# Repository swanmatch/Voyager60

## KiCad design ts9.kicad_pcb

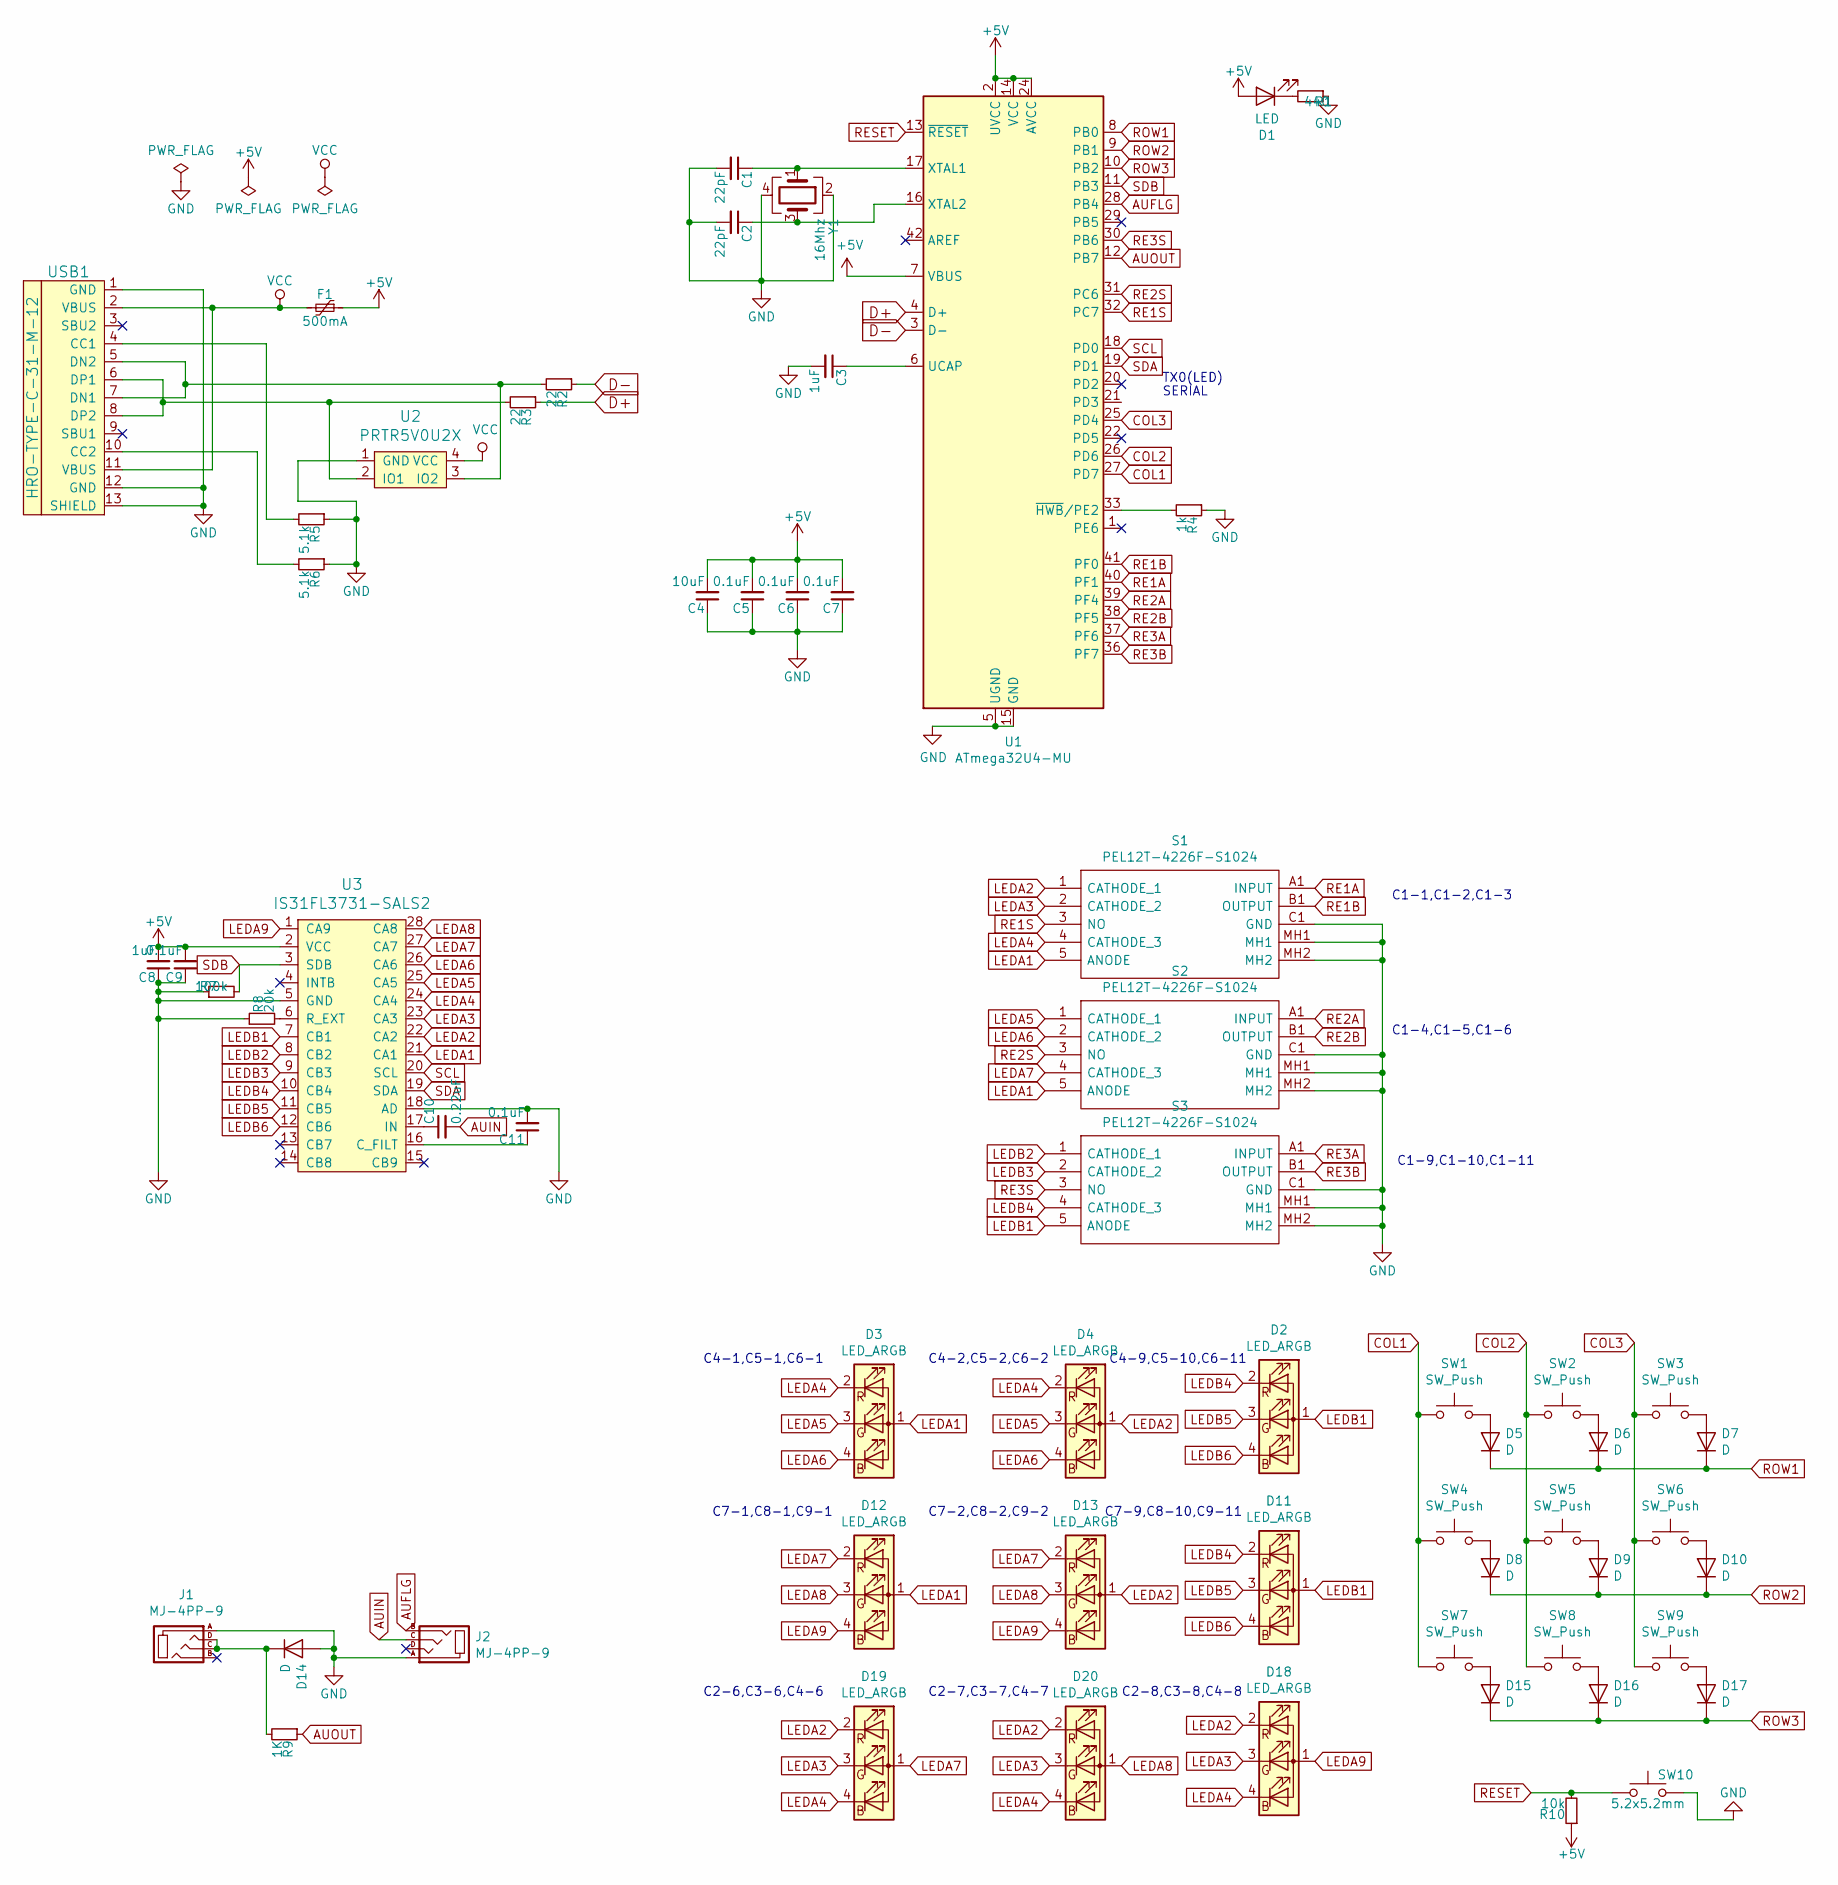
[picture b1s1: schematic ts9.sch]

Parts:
C1, C2: 22pF; C_0603
C3, C8: 1uF; C_0603
C4: 10uF; C_0603
C5, C6, C7, C9, C11: 0.1uF; C_0603
C10: 0.22uF; C_0603
D1: LED; LED_D3.0mm
D2, D3, D4, D11, D12, D13, D18, D19, D20: LED_ARGB; LED_Kingbright_AAA3528ESGCT
D5, D6, D7, D8, D9, D10, D14, D15, D16, D17: D; D_SOD-123
F1: 500mA; Fuse_SMD1206_Reflow
J1, J2: MJ-4PP-9; MJ-4PP-9_1side
R1: 440; R_0805
R2, R3: 22; R_0805
R4: 1k; R_0805
R5, R6: 5.1k; R_0805
R7: 100k; R_0805
R8: 20k; R_0805
R9: 1K; R_0805
R10: 10k; R_0805
S1, S2, S3: PEL12T-4226F-S1024; PEL12T4226FS1024; Manufacturer_Part_Number PEL12T-4226F-S1024; Mouser Part Number 652-PEL12T4226FS1024
SW1, SW2, SW3, SW4, SW5, SW6, SW7, SW8, SW9: SW_Push; PG1350
SW10: 5.2x5.2mm; ResetSW_1side
U1: ATmega32U4-MU; TQFP-44-1EP_10x10mm_Pitch0.8mm
U2: PRTR5V0U2X; SOT143B
U3: IS31FL3731-SALS2; SOP65P780X200-28N
USB1: HRO-TYPE-C-31-M-12; HRO-TYPE-C-31-M-12-Assembly
Y1: 16Mhz; Crystal_SMD_3225-4pin_3.2x2.5mm

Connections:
+5V: C4.2, C5.2, C6.2, C7.2, C8.2, C9.2, D1.2 (A), F1.1, R10.1, U1.2 (UVCC), U1.7 (VBUS), U1.14 (VCC), U1.24 (AVCC), U1.34 (VCC), U1.44 (AVCC), U3.2 (VCC)
AUFLG: J2.B, U1.28 (PB4)
AUIN: C10.2, J2.C
AUOUT: R9.1, U1.12 (PB7)
COL1: SW1.1, SW4.1, SW7.1, U1.27 (PD7)
COL2: SW2.1, SW5.1, SW8.1, U1.26 (PD6)
COL3: SW3.1, SW6.1, SW9.1, U1.25 (PD4)
D+: R3.1, U1.4 (D+)
D-: R2.1, U1.3 (D-)
GND: C1.2, C2.2, C3.2, C4.1, C5.1, C6.1, C7.1, C8.1, C9.1, C11.2, D14.2 (A), J1.A, J2.A, R1.1, R4.1, R5.1, R6.1, R7.1, R8.1, S1.C1 (GND), S1.MH1, S1.MH2, S2.C1 (GND), S2.MH1, S2.MH2, S3.C1 (GND), S3.MH1, S3.MH2, SW10.2, U1.5 (UGND), U1.15 (GND), U1.23 (GND), U1.35 (GND), U1.43 (GND), U1.45 (GND), U2.1 (GND), U3.5 (GND), U3.18 (AD), USB1.1 (GND), USB1.12 (GND), USB1.13 (SHIELD), Y1.2, Y1.4
LEDA1: D3.1 (A), D12.1 (A), S1.5 (ANODE), S2.5 (ANODE), U3.21 (CA1)
LEDA2: D4.1 (A), D13.1 (A), D18.2 (RK), D19.2 (RK), D20.2 (RK), S1.1 (CATHODE_1), U3.22 (CA2)
LEDA3: D18.3 (GK), D19.3 (GK), D20.3 (GK), S1.2 (CATHODE_2), U3.23 (CA3)
LEDA4: D3.2 (RK), D4.2 (RK), D18.4 (BK), D19.4 (BK), D20.4 (BK), S1.4 (CATHODE_3), U3.24 (CA4)
LEDA5: D3.3 (GK), D4.3 (GK), S2.1 (CATHODE_1), U3.25 (CA5)
LEDA6: D3.4 (BK), D4.4 (BK), S2.2 (CATHODE_2), U3.26 (CA6)
LEDA7: D12.2 (RK), D13.2 (RK), D19.1 (A), S2.4 (CATHODE_3), U3.27 (CA7)
LEDA8: D12.3 (GK), D13.3 (GK), D20.1 (A), U3.28 (CA8)
LEDA9: D12.4 (BK), D13.4 (BK), D18.1 (A), U3.1 (CA9)
LEDB1: D2.1 (A), D11.1 (A), S3.5 (ANODE), U3.7 (CB1)
LEDB2: S3.1 (CATHODE_1), U3.8 (CB2)
LEDB3: S3.2 (CATHODE_2), U3.9 (CB3)
LEDB4: D2.2 (RK), D11.2 (RK), S3.4 (CATHODE_3), U3.10 (CB4)
LEDB5: D2.3 (GK), D11.3 (GK), U3.11 (CB5)
LEDB6: D2.4 (BK), D11.4 (BK), U3.12 (CB6)
unnamed: C1.1, U1.17 (XTAL1), Y1.1
unnamed: C2.1, U1.16 (XTAL2), Y1.3
unnamed: C3.1, U1.6 (UCAP)
unnamed: C10.1, U3.17 (IN)
unnamed: C11.1, U3.16 (C_FILT)
unnamed: D1.1 (K), R1.2
unnamed: D5.2 (A), SW1.2
unnamed: D6.2 (A), SW2.2
unnamed: D7.2 (A), SW3.2
unnamed: D8.2 (A), SW4.2
unnamed: D9.2 (A), SW5.2
unnamed: D10.2 (A), SW6.2
unnamed: D14.1 (K), J1.C, J1.D, R9.2
unnamed: D15.2 (A), SW7.2
unnamed: D16.2 (A), SW8.2
unnamed: D17.2 (A), SW9.2
unnamed: R2.2, U2.3 (IO2), USB1.5 (DN2), USB1.7 (DN1)
unnamed: R3.2, U2.2 (IO1), USB1.6 (DP1), USB1.8 (DP2)
unnamed: R4.2, U1.33 (~HWB~/PE2)
unnamed: R5.2, USB1.4 (CC1)
unnamed: R6.2, USB1.10 (CC2)
unnamed: R8.2, U3.6 (R_EXT)
RE1A: S1.A1 (INPUT), U1.40 (PF1)
RE1B: S1.B1 (OUTPUT), U1.41 (PF0)
RE1S: S1.3 (NO), U1.32 (PC7)
RE2A: S2.A1 (INPUT), U1.39 (PF4)
RE2B: S2.B1 (OUTPUT), U1.38 (PF5)
RE2S: S2.3 (NO), U1.31 (PC6)
RE3A: S3.A1 (INPUT), U1.37 (PF6)
RE3B: S3.B1 (OUTPUT), U1.36 (PF7)
RE3S: S3.3 (NO), U1.30 (PB6)
RESET: R10.2, SW10.1, U1.13 (~RESET)
ROW1: D5.1 (K), D6.1 (K), D7.1 (K), U1.8 (PB0)
ROW2: D8.1 (K), D9.1 (K), D10.1 (K), U1.9 (PB1)
ROW3: D15.1 (K), D16.1 (K), D17.1 (K), U1.10 (PB2)
SCL: U1.18 (PD0), U3.20 (SCL)
SDA: U1.19 (PD1), U3.19 (SDA)
SDB: R7.2, U1.11 (PB3), U3.3 (SDB)
VCC: F1.2, U2.4 (VCC), USB1.2 (VBUS), USB1.11 (VBUS)

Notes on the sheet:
TX0(LED)
C1-1,C1-2,C1-3
C1-4,C1-5,C1-6
C1-9,C1-10,C1-11
C4-1,C5-1,C6-1
C7-1,C8-1,C9-1
C4-2,C5-2,C6-2
C7-2,C8-2,C9-2
C4-9,C5-10,C6-11
C7-9,C8-10,C9-11
C2-6,C3-6,C4-6
C2-7,C3-7,C4-7
C2-8,C3-8,C4-8
SERIAL

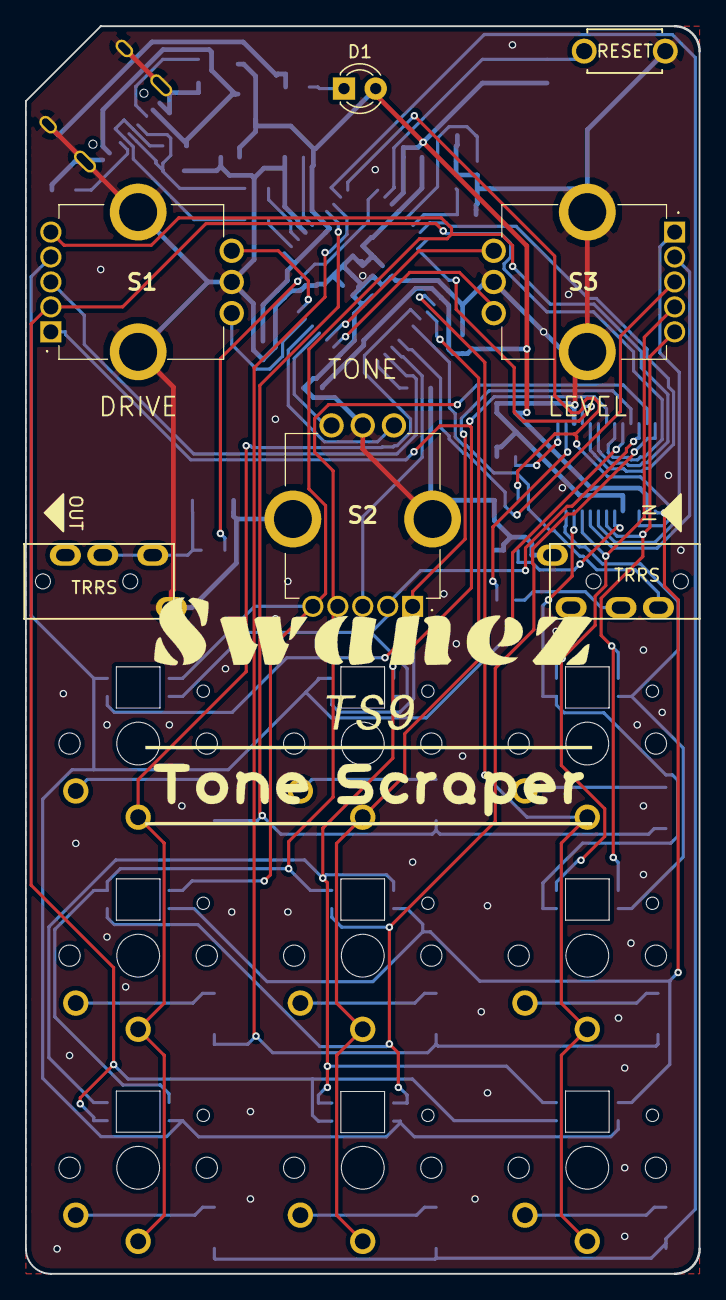
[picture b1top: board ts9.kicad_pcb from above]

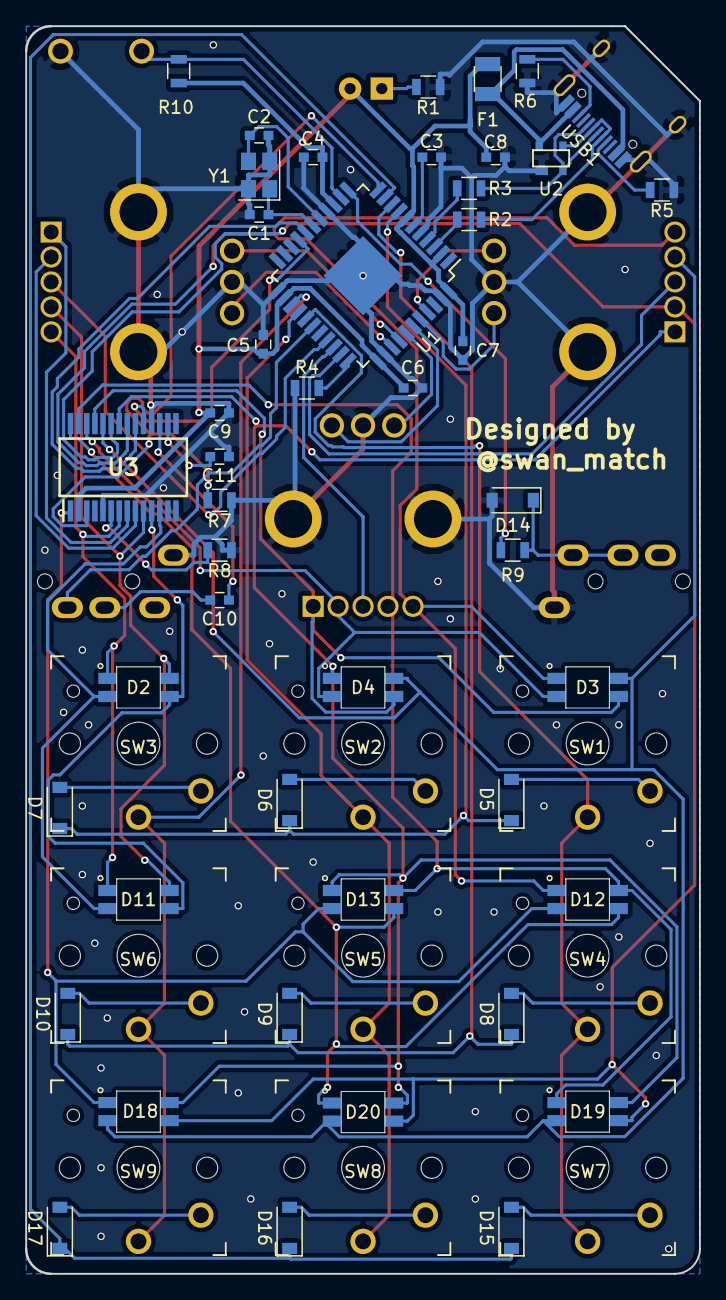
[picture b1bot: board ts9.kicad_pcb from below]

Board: 2 copper layers, 54.0 x 100.0 mm, 62 parts (46 on the bottom side), 64 nets.

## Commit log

2019-11-16 bete
2019-11-16 beta
2019-12-19 first order
2020-02-24 review kobayuta
